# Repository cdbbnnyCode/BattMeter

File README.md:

## BattMeter  
   
BattMeter is a simple voltage meter for FTC batteries. The voltage ranges can be adjusted by changing the values of
r1, r2, r3, r4, and r5 (see [v1.2_voltages.txt](/v1.2_voltages.txt) for default resistor values).  
The board has an XT30 plug to connect REV batteries directly. If you have a different type of connector on your batteries, you can:
* Use an adapter plug
* Use a short length of wire and solder your connector onto that (recommended for crimped connectors like Tamiya and Anderson Powerpoles)
* Modify the board to fit your connector

### Usage
To edit these files, you need Autodesk Eagle. If you just want to fabricate a board, you should be able to find Gerber files under
the Releases page. You can find a list of the components you need under [bom.txt](/bom.txt).  
The PCB design and schematic are licensed under the [Creative Commons Attribution-ShareAlike 4.0 License](https://creativecommons.org/licenses/by-sa/4.0/).

### How it works
This meter uses four op-amp comparators to turn on the LEDs at specific input voltages.  
  
A voltage divider reduces the battery voltage to somewhere around 5V, and the regulator provides a (reasonably) fixed 5V reference.  
  
The chain of resistors (r1, r2, r3, r4, and r5) drop the regulated voltage at specific steps, and the op-amps compare the scaled
battery voltage with this voltage. The logic is inverted--the input voltage is connected to the inverting input--because the LED
turns on when the op-amp's output is pulled to GND.

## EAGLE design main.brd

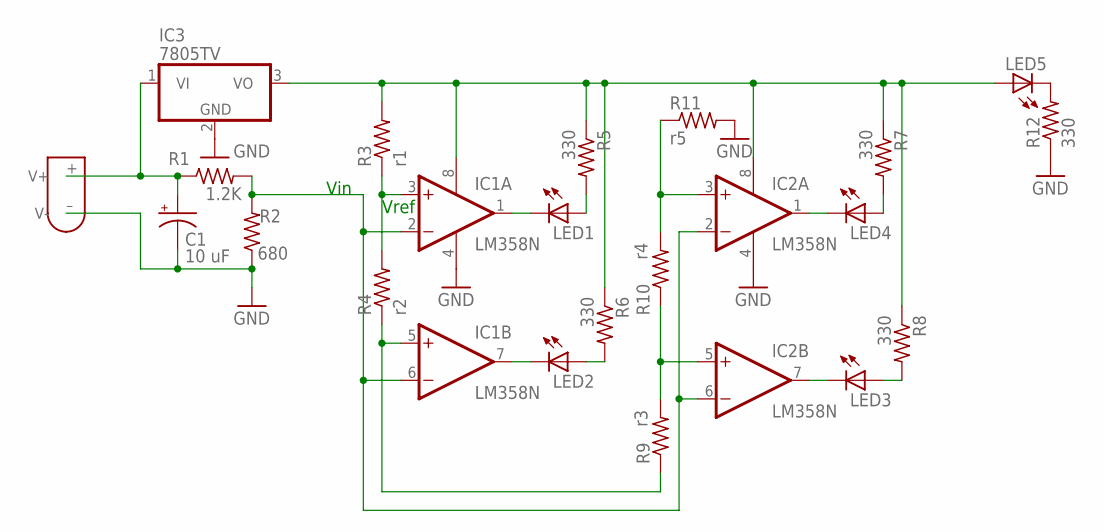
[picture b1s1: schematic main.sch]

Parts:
C1: 10 uF; E2-5
IC1, IC2: LM358N; DIL08
IC3: 7805TV; TO220V
LED1, LED2, LED3, LED4, LED5: LED5MM
R1: 1.2K; 0207/7
R2: 680; 0207/7
R3: r1; 0207/7
R4: r2; 0207/7
R5, R6, R7, R8, R12: 330; 0207/7
R9: r3; 0207/7
R10: r4; 0207/7
R11: r5; 0207/7
U$1: XT30

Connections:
GND: C1.-, IC1.4 (V-), IC2.4 (V-), IC3.2 (GND), R2.1, R11.2, R12.1, U$1.– (V-)
unnamed: IC1.3 (+IN), R3.1, R4.2
unnamed: C1.+, IC3.1 (VI), R1.1, U$1.+ (V+)
unnamed: IC1.8 (V+), IC2.8 (V+), IC3.3 (VO), LED5.A, R3.2, R5.1, R6.1, R7.1, R8.1
unnamed: IC1.5 (+IN), R4.1, R9.1
unnamed: IC1.1 (OUT), LED1.K (C)
unnamed: LED1.A, R5.2
unnamed: LED2.A, R6.2
unnamed: IC1.7 (OUT), LED2.K (C)
unnamed: IC2.1 (OUT), LED4.K (C)
unnamed: LED4.A, R7.2
unnamed: IC2.7 (OUT), LED3.K (C)
unnamed: LED3.A, R8.2
unnamed: IC1.2 (-IN), IC1.6 (-IN), IC2.2 (-IN), IC2.6 (-IN), R1.2, R2.2
unnamed: IC2.5 (+IN), R9.2, R10.1
unnamed: IC2.3 (+IN), R10.2, R11.1
unnamed: LED5.K (C), R12.2

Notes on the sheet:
Vref
Vin

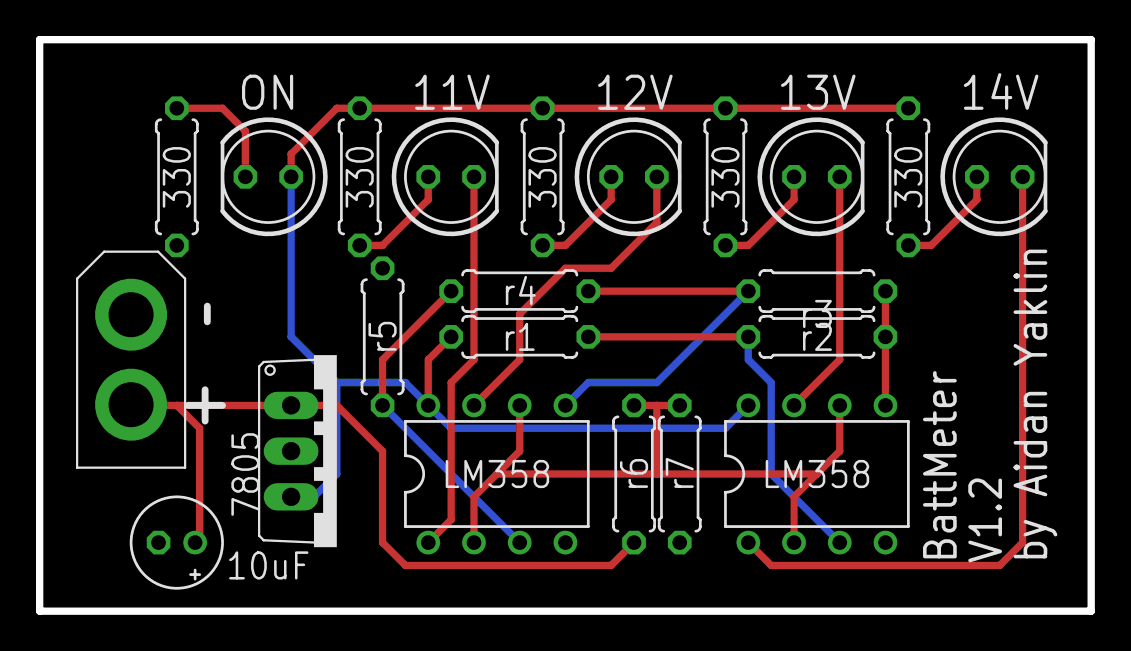
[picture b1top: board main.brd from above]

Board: 2 copper layers, 58.4 x 31.8 mm, 23 parts (0 on the bottom side), 17 nets.

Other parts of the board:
U$2: LOGO

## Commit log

2019-03-13 Initial commit (V1.2)
2019-03-13 Remove versioned files
2019-03-13 Add README skeleton
2019-03-14 Add README images
2019-03-14 Add links and images to the README
2019-03-14 Add newline :P
2019-03-14 Add link to CC license
2019-03-16 Add BOM
2019-03-23 Add real board photo
2019-03-25 Fix resistor values
